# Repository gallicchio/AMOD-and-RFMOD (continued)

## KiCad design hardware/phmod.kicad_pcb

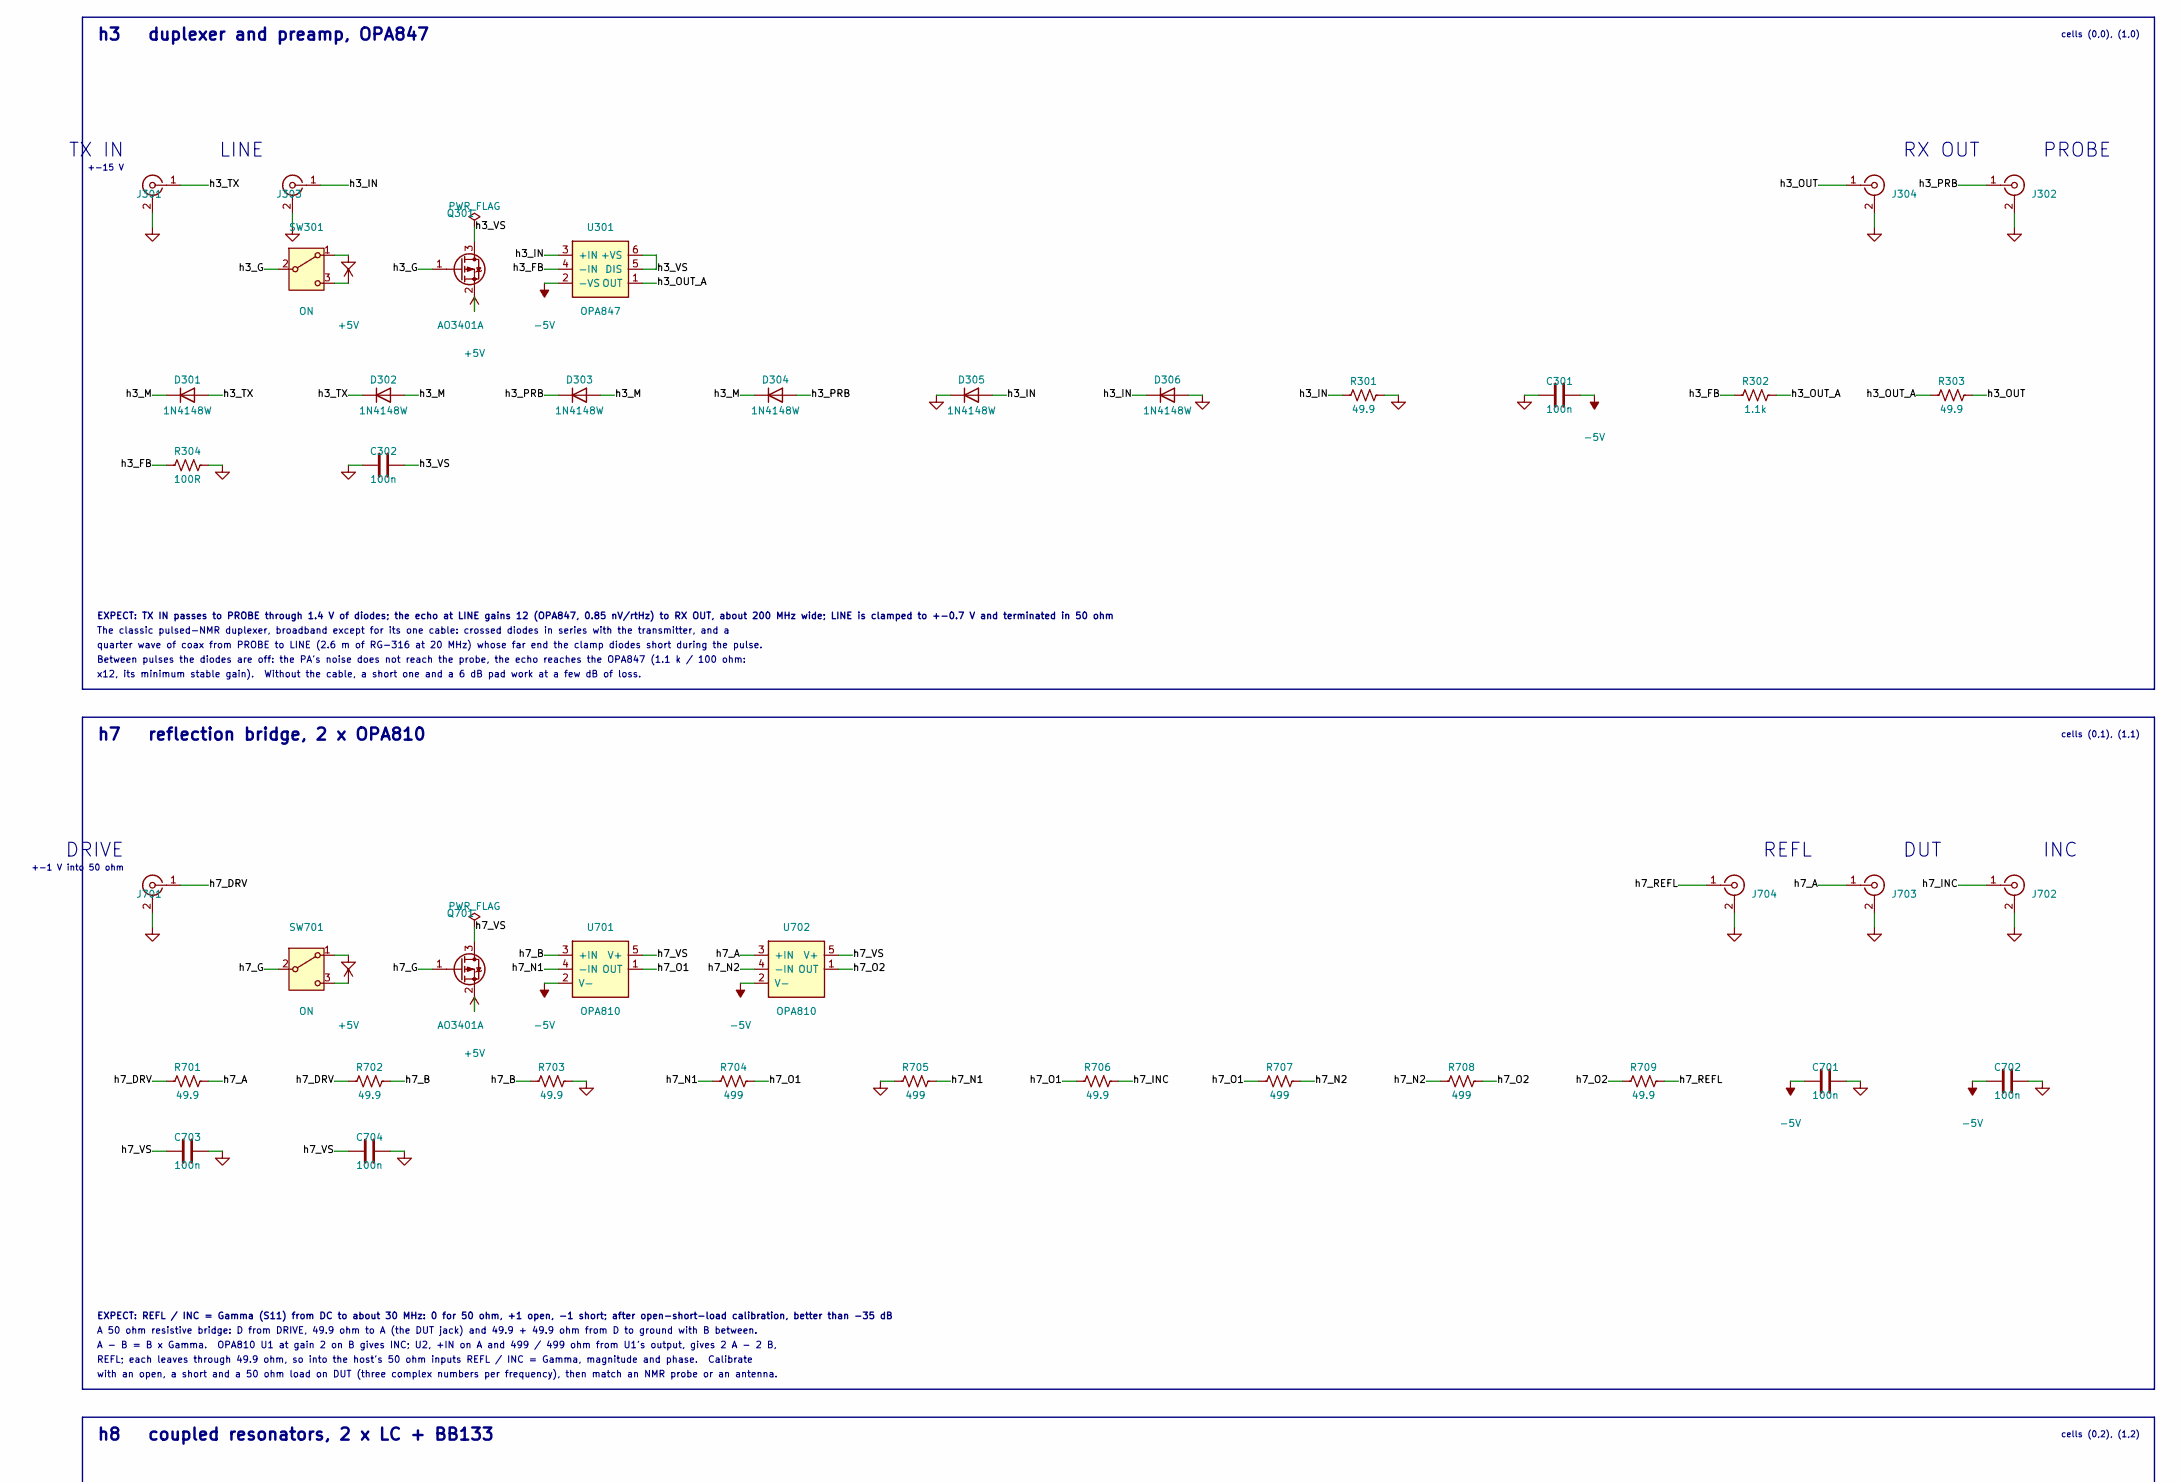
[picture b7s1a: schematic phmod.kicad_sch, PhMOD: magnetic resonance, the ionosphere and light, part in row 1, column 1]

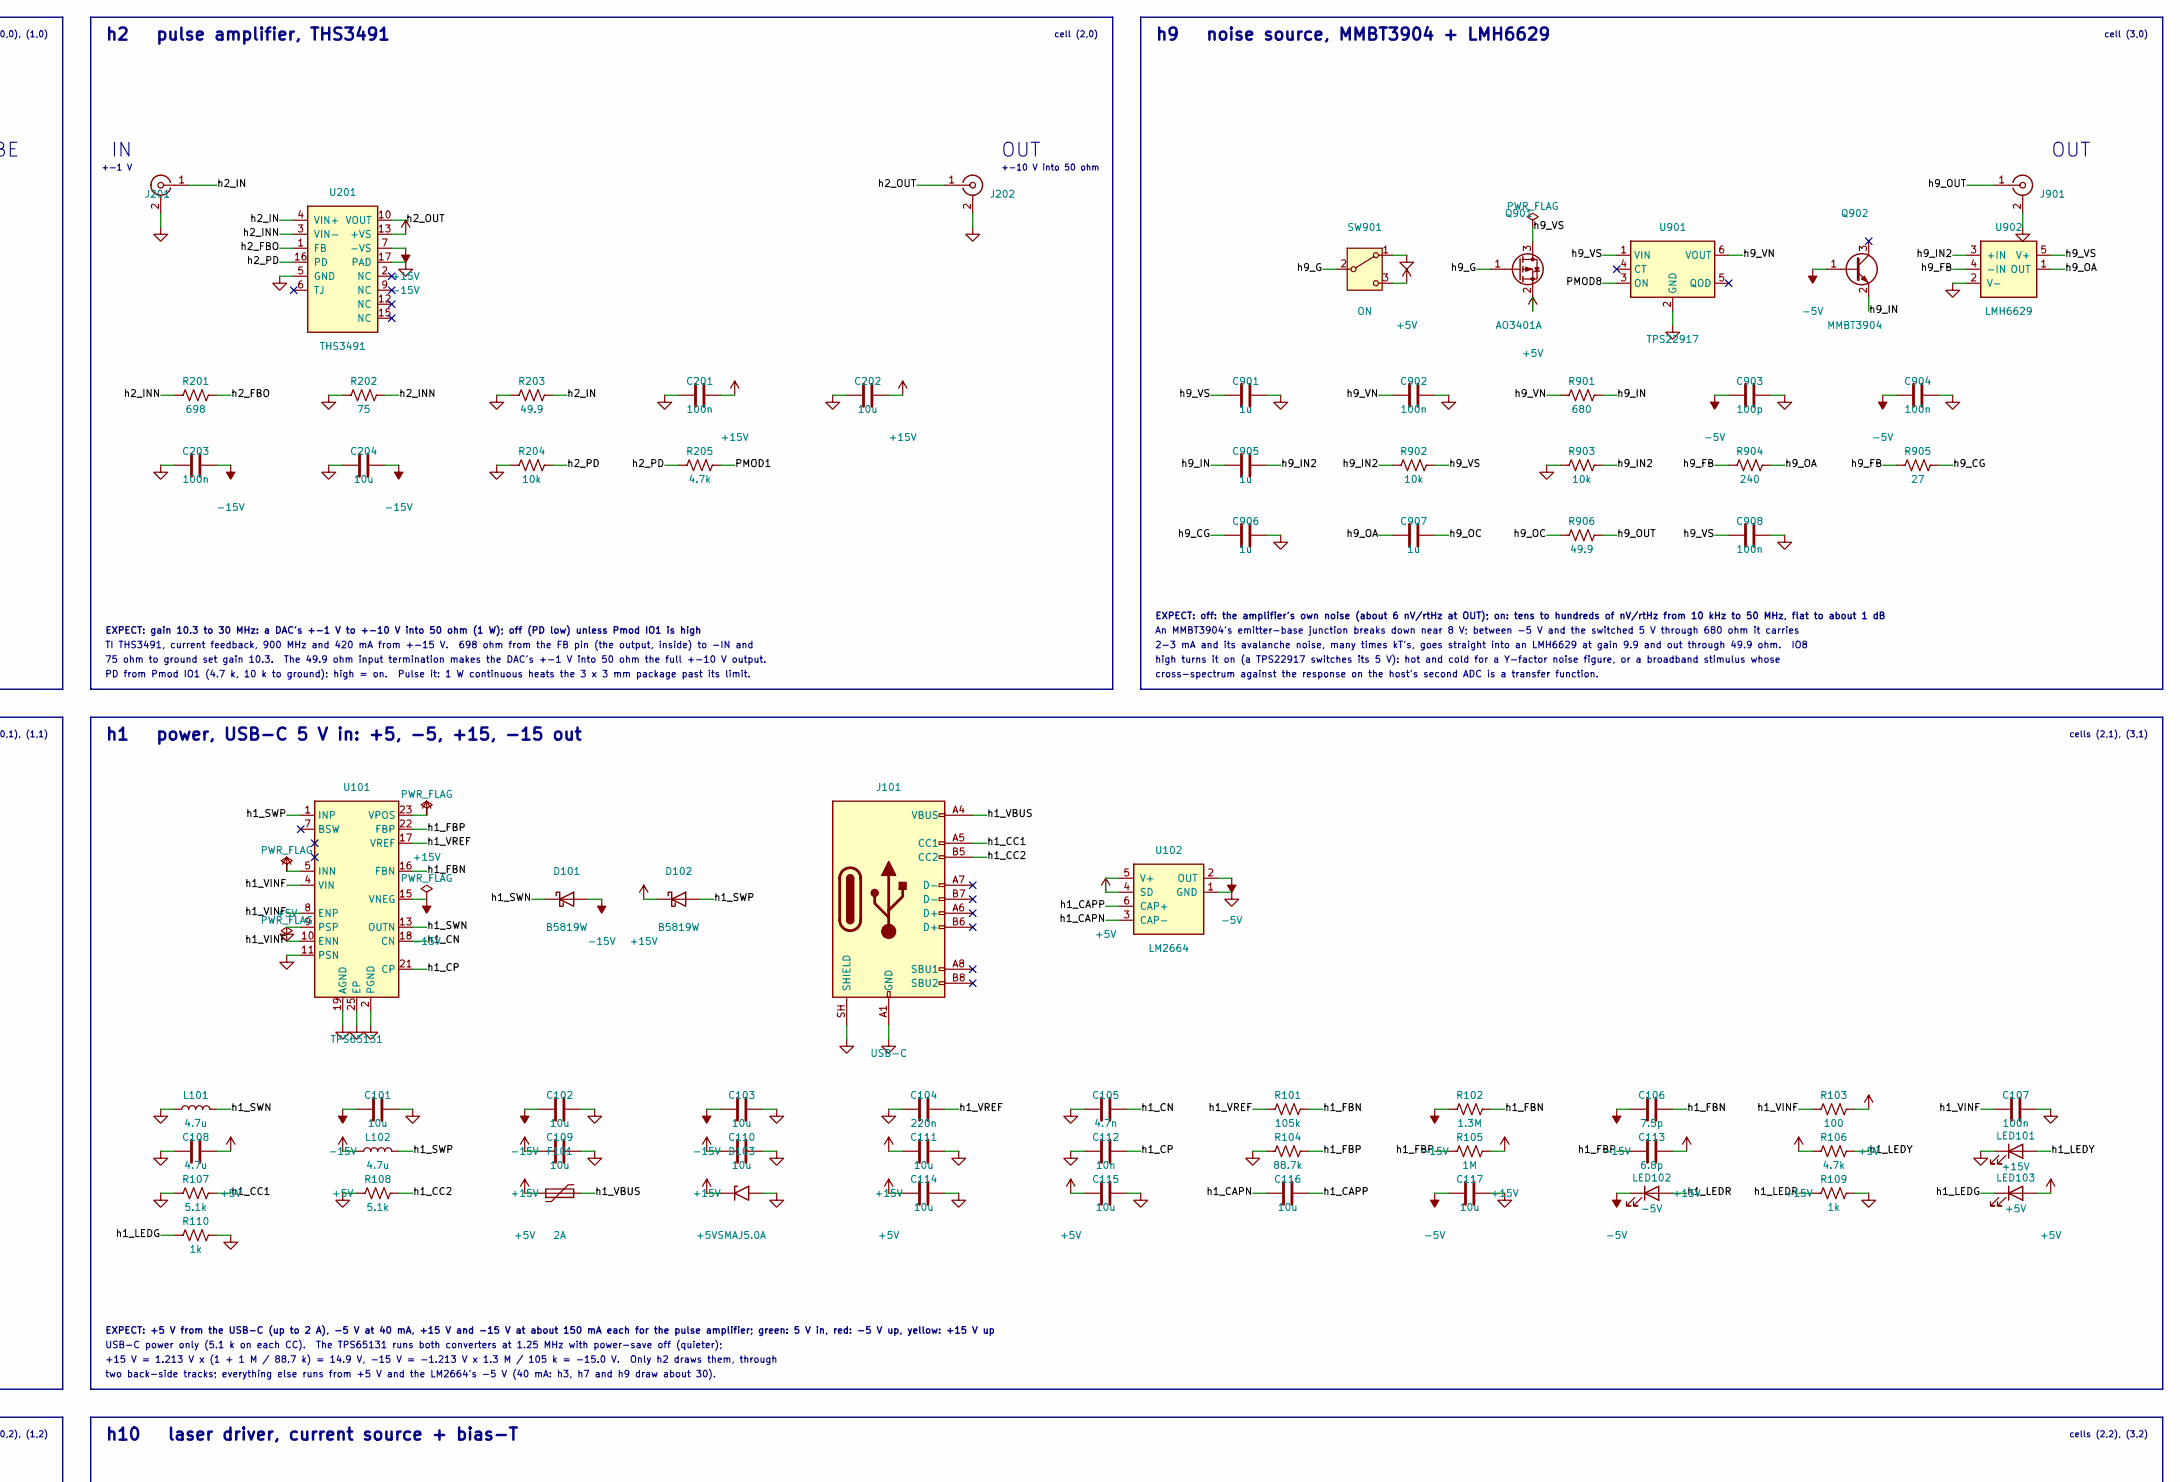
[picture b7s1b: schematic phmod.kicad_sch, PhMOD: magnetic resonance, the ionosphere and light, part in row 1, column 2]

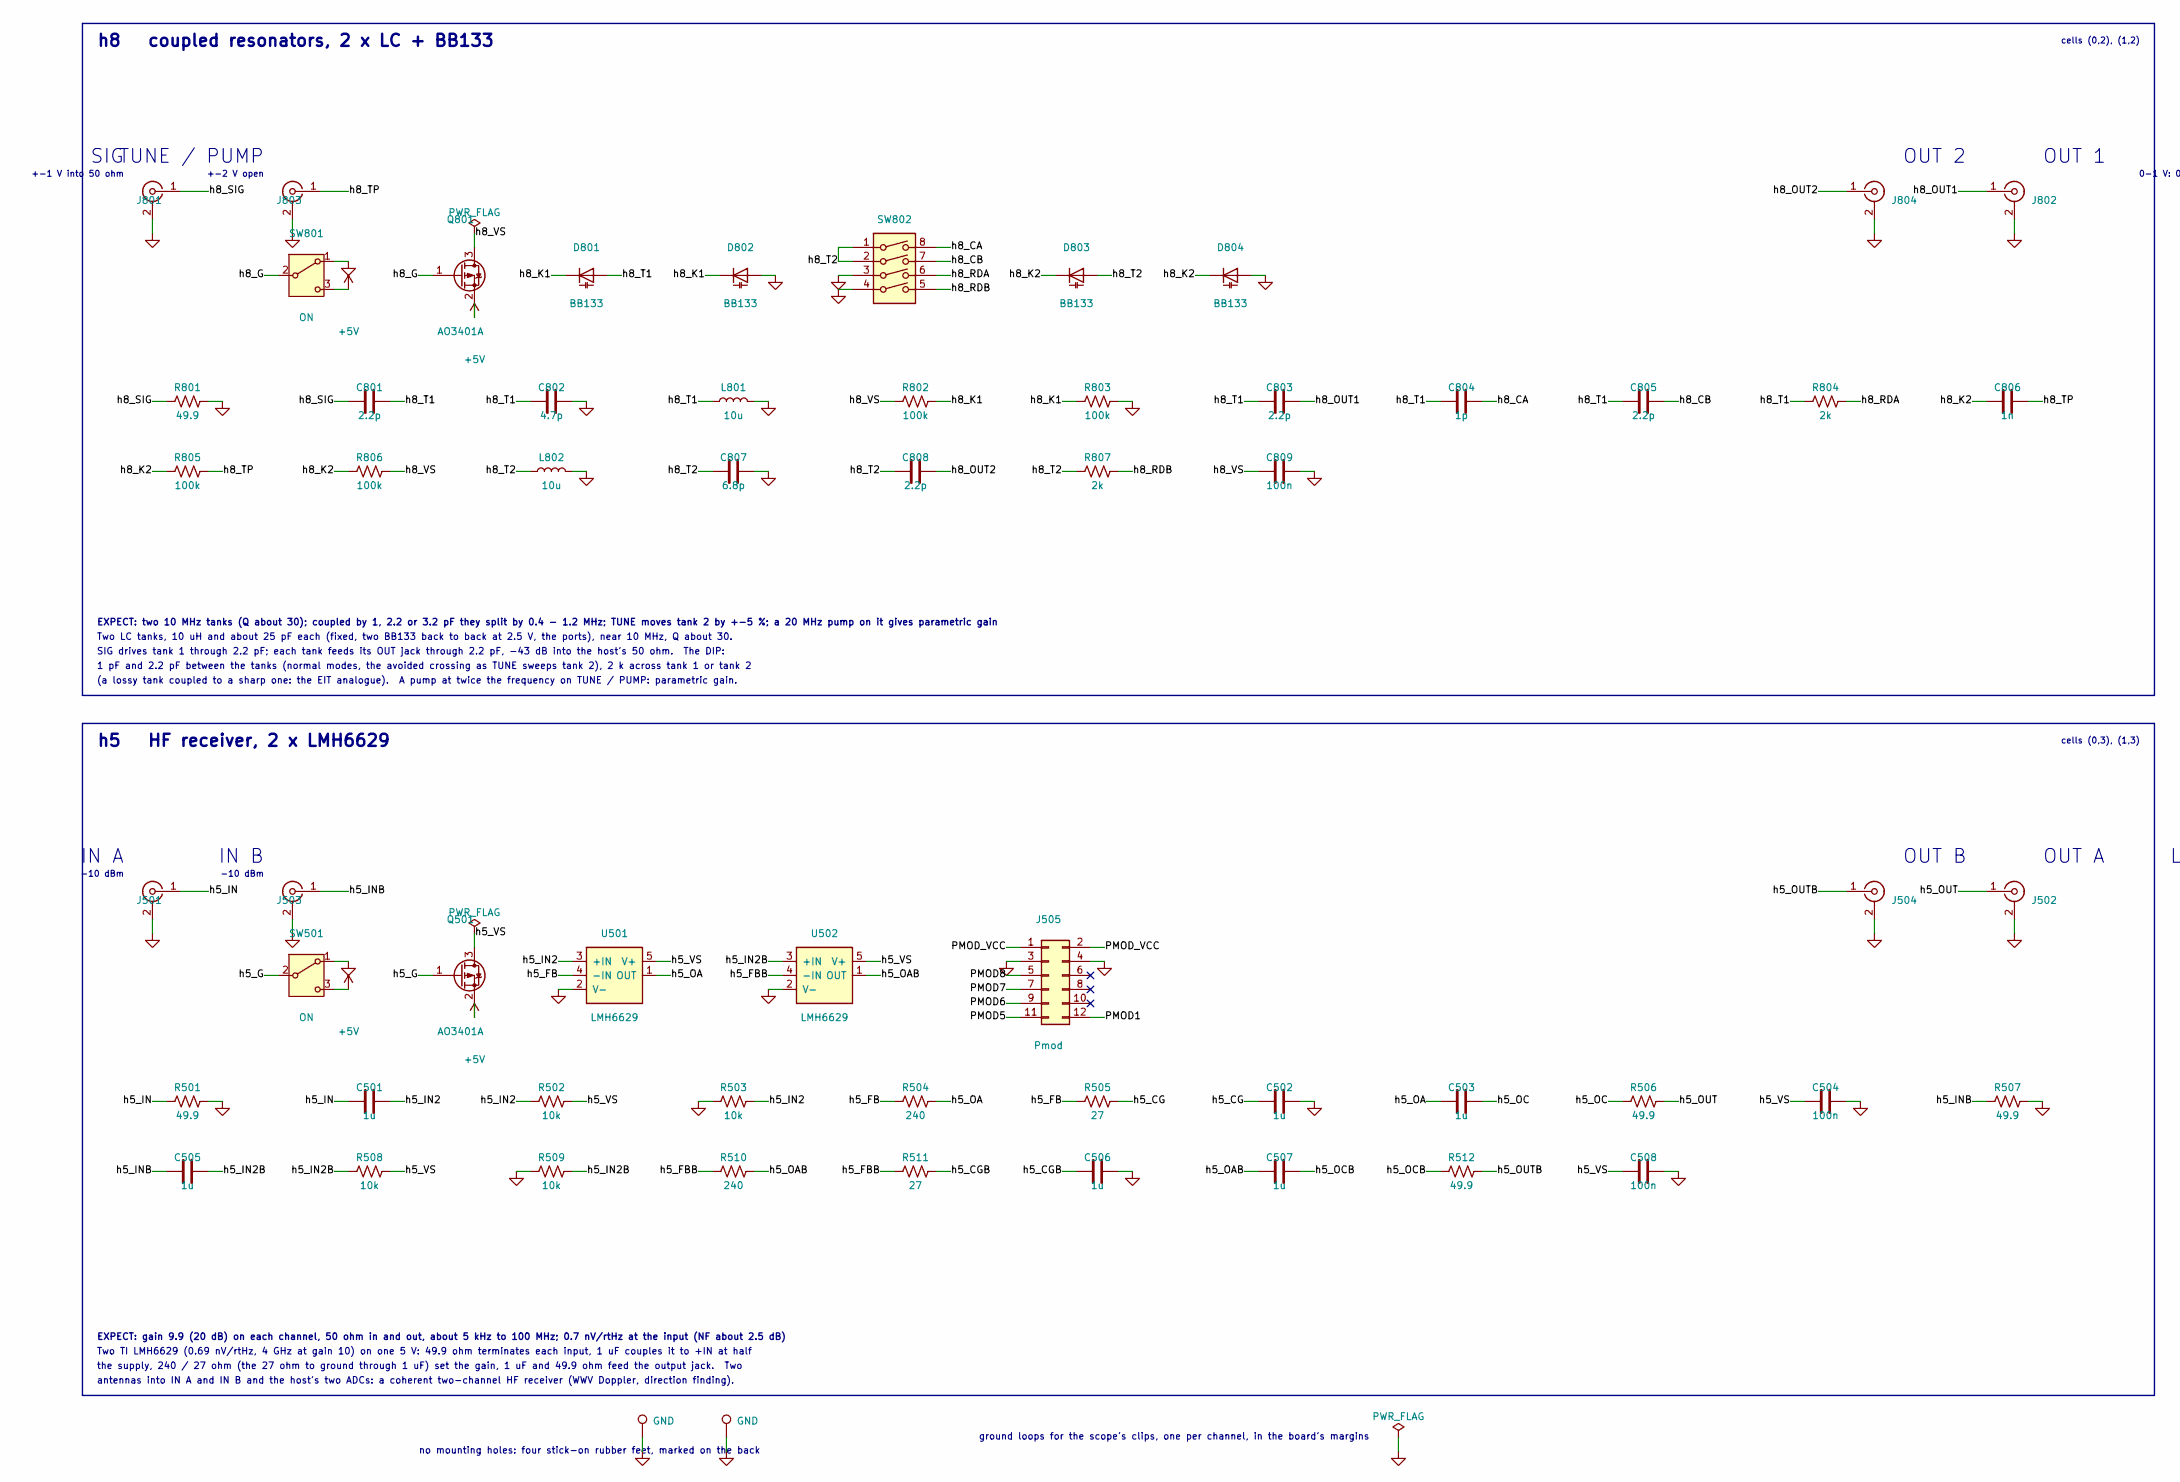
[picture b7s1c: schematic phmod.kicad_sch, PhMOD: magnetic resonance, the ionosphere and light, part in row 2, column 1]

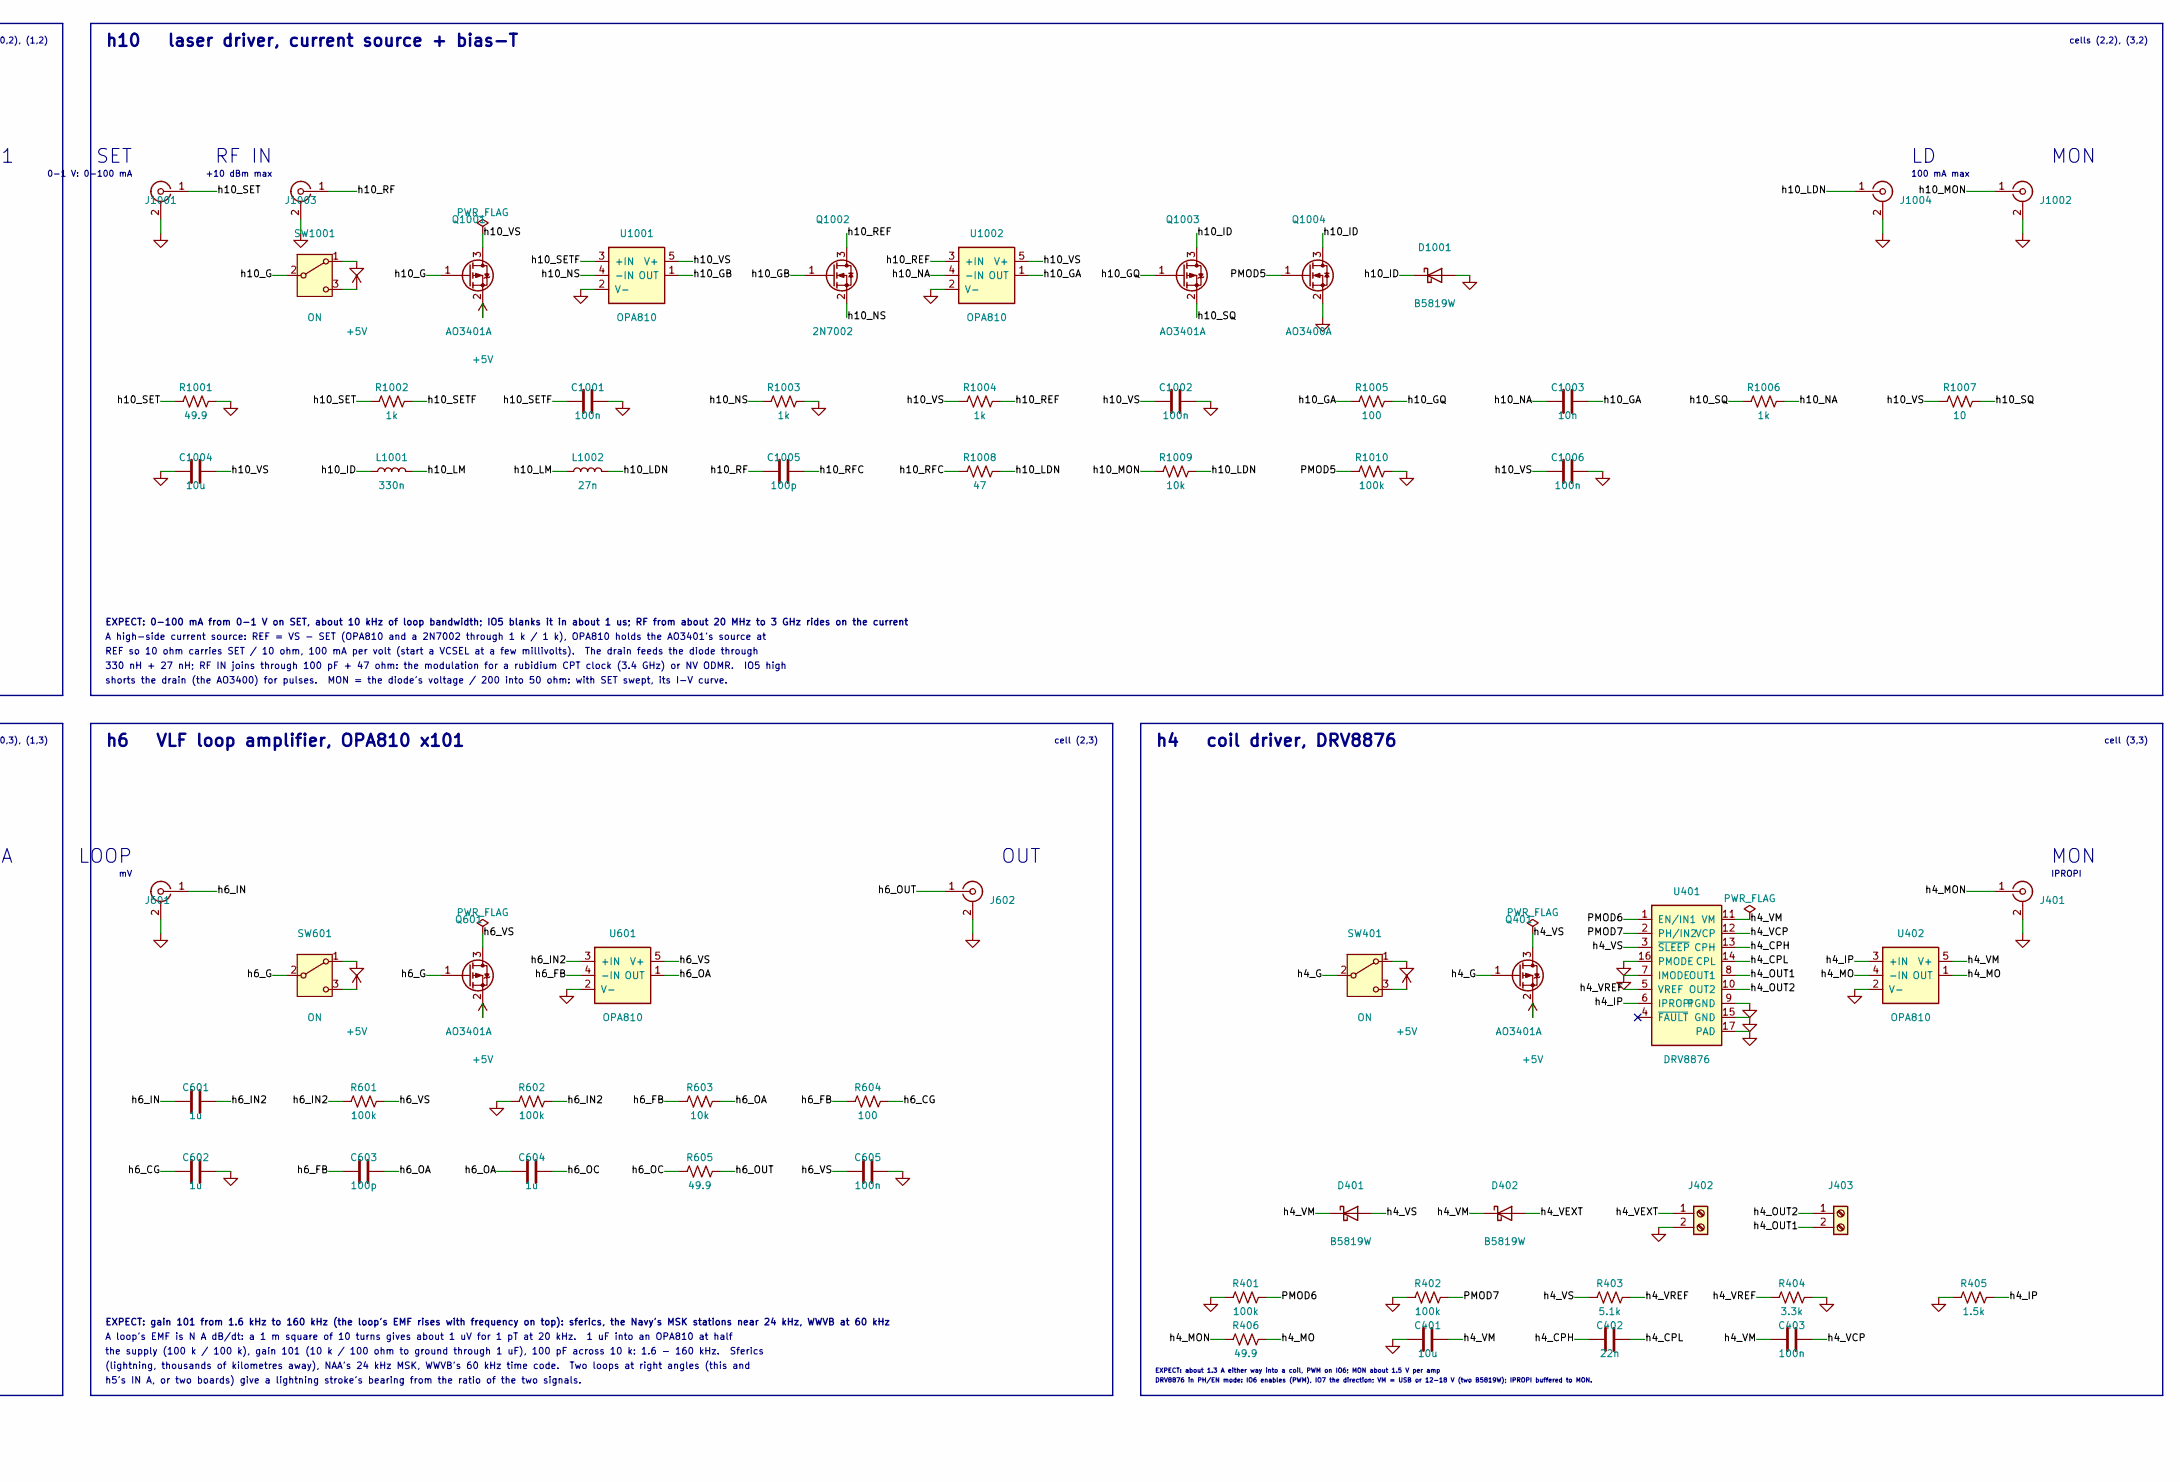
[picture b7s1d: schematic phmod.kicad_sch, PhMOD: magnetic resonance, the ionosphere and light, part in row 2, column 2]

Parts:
C101, C102, C103, C109, C110, C111, C114, C115, C116, C117, C202, C204, C401, C1004: 10u; C_0805_2012Metric; MPN CL21A106KAYNNNE; LCSC C15850
C104: 220n; C_0402_1005Metric; MPN CL05B224KO5NNNC; LCSC C16772
C105: 4.7n; C_0402_1005Metric; MPN CL05B472KB5NNNC; LCSC C84705
C106: 7.5p; C_0402_1005Metric; MPN 0402CG7R5C500NT; LCSC C43514
C107, C201, C203, C403, C504, C508, C605, C701, C702, C703, C704, C809, C902, C904, C908, C1001, C1002, C1006: 100n; C_0402_1005Metric; MPN CL05B104KO5NNNC; LCSC C1525
C108: 4.7u; C_0805_2012Metric; MPN CL21A475KAQNNNE; LCSC C1779
C112, C1003: 10n; C_0402_1005Metric; MPN CL05B103KB5NNNC; LCSC C15195
C113, C807: 6.8p; C_0402_1005Metric; MPN 0402CG6R8C500NT; LCSC C1576
C301, C302: 100n; C_0603_1608Metric; MPN CC0603KRX7R9BB104; LCSC C14663
C402: 22n; C_0402_1005Metric; MPN CL05B223KB5NNNC; LCSC C337699
C501, C502, C503, C505, C506, C507, C601, C602, C604, C901, C905, C906, C907: 1u; C_0402_1005Metric; MPN CL05A105KP5NNNC; LCSC C14445
C603, C903, C1005: 100p; C_0402_1005Metric; MPN 0402CG101J500NT; LCSC C1546
C801, C803, C805, C808: 2.2p; C_0402_1005Metric; MPN 0402CG2R2C500NT; LCSC C1559
C802: 4.7p; C_0402_1005Metric; MPN 0402CG4R7C500NT; LCSC C1569
C804: 1p; C_0402_1005Metric; MPN 0402CG1R0C500NT; LCSC C1550
C806: 1n; C_0402_1005Metric; MPN 0402B102K500NT; LCSC C1523
D101, D102, D401, D402, D1001: B5819W; D_SOD-123; MPN B5819W; LCSC C64885
D103: SMAJ5.0A; D_SMA; MPN SMAJ5.0A; LCSC C78401
D301, D302, D303, D304, D305, D306: 1N4148W; D_SOD-123; MPN 1N4148W; LCSC C81598
D801, D802, D803, D804: BB133; D_SOD-323; MPN BB133; LCSC C5334579
F101: 2A; Fuse_1812_4532Metric; MPN MF-MSMF200-2; LCSC C210837
J101: USB-C; USB_C_Receptacle_HRO_TYPE-C-31-M-12; MPN TYPE-C-31-M-12; LCSC C165948
J201, J202, J301, J302, J303, J304, J401, J501, J502, J503, J504, J601, J602, J701, J702, J703, J704, J801, J802, J803, J804, J901, J1001, J1002, J1003, J1004: SMA; SMA_BWSMA-KE-Z001_Vertical; MPN BWSMA-KE-Z001; LCSC C496549
J402: VM in; TerminalBlock_KF301_1x02_P5.00mm; MPN KF301-5.0-2P; LCSC C474881
J403: coil; TerminalBlock_KF301_1x02_P5.00mm; MPN KF301-5.0-2P; LCSC C474881
J505: Pmod; PinHeader_2x06_P2.54mm_Horizontal_PZ254R-12-12P; MPN PZ254R-12-12P; LCSC C492434
L101, L102: 4.7u; L_4x4_XRNR4030; MPN SWPA4030S4R7MT; LCSC C57269
L801, L802: 10u; L_1210_3225Metric; MPN NLV32T-100J-PF; LCSC C76835
L1001: 330n; L_0805_2012Metric; MPN SDWL2012CR33JSTF; LCSC C98210
L1002: 27n; L_0402_1005Metric; MPN LQW15AN27NG80D; LCSC C882469
LED101: +15V; LED_0805_2012Metric_Kbar; MPN KT-0805Y; LCSC C2296
LED102: -5V; LED_0805_2012Metric_Kbar; MPN NCD0805R1; LCSC C84256
LED103: +5V; LED_0805_2012Metric_Kbar; MPN KT-0805G; LCSC C2297
Q301, Q401, Q501, Q601, Q701, Q801, Q901, Q1001, Q1003: AO3401A; SOT-23; MPN AO3401A; LCSC C15127
Q902: MMBT3904; SOT-23; MPN MMBT3904(RANGE:100-300); LCSC C20526
Q1002: 2N7002; SOT-23; MPN 2N7002; LCSC C8545
Q1004: AO3400A; SOT-23; MPN AO3400A; LCSC C20917
R101: 105k; R_0402_1005Metric; MPN 0402WGF1053TCE; LCSC C25742
R102: 1.3M; R_0402_1005Metric; MPN 0402WGF1304TCE; LCSC C423245
R103, R604, R1005: 100; R_0402_1005Metric; MPN 0402WGF1000TCE; LCSC C25076
R104: 88.7k; R_0402_1005Metric; MPN 0402WGF8872TCE; LCSC C25922
R105: 1M; R_0402_1005Metric; MPN 0402WGF1004TCE; LCSC C26083
R106: 4.7k; R_0805_2012Metric; MPN 0805W8F4701T5E; LCSC C17673
R107, R108: 5.1k; R_0805_2012Metric; MPN 0805W8F5101T5E; LCSC C27834
R109, R110: 1k; R_0805_2012Metric; MPN 0805W8F1001T5E; LCSC C17513
R201: 698; R_0402_1005Metric; MPN 0402WGF6980TCE; LCSC C33359
R202: 75; R_0402_1005Metric; MPN 0402WGF750JTCE; LCSC C25133
R203, R301, R406, R501, R506, R507, R512, R605, R701, R702, R703, R706, R709, R801, R906, R1001: 49.9; R_0402_1005Metric; MPN CRCW040249R9FKEDHP; LCSC C844112
R204, R502, R503, R508, R509, R603, R902, R903, R1009: 10k; R_0402_1005Metric; MPN 0402WGF1002TCE; LCSC C25744
R205: 4.7k; R_0402_1005Metric; MPN 0402WGF4701TCE; LCSC C25900
R302: 1.1k; R_0603_1608Metric; MPN 0603WAF1101T5E; LCSC C22764
R303: 49.9; R_0603_1608Metric; MPN SR0603FR-7T49R9L; LCSC C6230117
R304: 100R; R_0603_1608Metric; MPN 0603WAF1000T5E; LCSC C22775
R401, R402, R601, R602, R802, R803, R805, R806, R1010: 100k; R_0402_1005Metric; MPN 0402WGF1003TCE; LCSC C25741
R403: 5.1k; R_0402_1005Metric; MPN 0402WGF5101TCE; LCSC C25905
R404: 3.3k; R_0402_1005Metric; MPN 0402WGF3301TCE; LCSC C25890
R405: 1.5k; R_0402_1005Metric; MPN 0402WGF1501TCE; LCSC C25867
R504, R510, R904: 240; R_0402_1005Metric; MPN 0402WGF2400TCE; LCSC C25094
R505, R511, R905: 27; R_0402_1005Metric; MPN CR0402FF27R0G; LCSC C100353
R704, R705, R707, R708: 499; R_0402_1005Metric; MPN 0402WGF4990TCE; LCSC C4125
R804, R807: 2k; R_0402_1005Metric; MPN 0402WGF2001TCE; LCSC C4109
R901: 680; R_0402_1005Metric; MPN 0402WGF6800TCE; LCSC C25130
R1002, R1003, R1004, R1006: 1k; R_0402_1005Metric; MPN 0402WGF1001TCE; LCSC C11702
R1007: 10; R_0805_2012Metric; MPN 0805W8F100JT5E; LCSC C17415
R1008: 47; R_0402_1005Metric; MPN 0402WGF470JTCE; LCSC C25118
SW301, SW401, SW501, SW601, SW701, SW801, SW901, SW1001: ON; SW_SPDT_Shouhan_MSK12C02; MPN MSK12C02; LCSC C431540
SW802: DIP4; SW_DIP_SPSTx04_Slide_1.27mm_DSHP04; MPN DSHP04TSGET; LCSC C40736
TP9901, TP9902: GND; TestPoint_Loop_RH-5019; MPN RH-5019; LCSC C5199800
U101: TPS65131; QFN-24-1EP_4x4mm_P0.5mm_EP2.7x2.7mm; MPN TPS65131RGER; LCSC C87663
U102: LM2664; SOT-23-6; MPN LM2664M6X/NOPB; LCSC C108573
U201: THS3491; QFN-16-1EP_3x3mm_P0.5mm_EP1.7x1.7mm; MPN THS3491IRGTR; LCSC C2058688
U301: OPA847; SOT-23-6; MPN OPA847IDBVT; LCSC C2059024
U401: DRV8876; HTSSOP-16-1EP_4.4x5mm_P0.65mm_EP3.4x5mm_Mask2.66x2.46mm; MPN DRV8876PWPR; LCSC C575551
U402, U601, U701, U702, U1001, U1002: OPA810; SOT-23-5; MPN OPA810IDBVR; LCSC C2833513
U501, U502, U902: LMH6629; SOT-23-5; MPN LMH6629MFX/NOPB; LCSC C2059678
U901: TPS22917; SOT-23-6; MPN TPS22917DBVR; LCSC C2681320

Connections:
+5V: C108.2, C114.1, C115.1, D103.1 (A1), F101.1, L102.1, LED103.2 (A), Q301.2 (S), Q401.2 (S), Q501.2 (S), Q601.2 (S), Q701.2 (S), Q801.2 (S), Q901.2 (S), Q1001.2 (S), R103.2, SW301.3 (C), SW401.3 (C), SW501.3 (C), SW601.3 (C), SW701.3 (C), SW801.3 (C), SW901.3 (C), SW1001.3 (C), U101.5 (INN), U101.6 (INN), U102.4 (SD), U102.5 (V+)
+15V: C109.1, C110.1, C111.1, C113.2, C201.2, C202.2, D102.1 (K), R105.2, R106.1, U101.23 (VPOS), U201.13 (+VS), U201.14 (+VS)
-5V: C117.1, C301.2, C701.1, C702.1, C903.1, C904.1, LED102.1 (K), Q902.1 (B), U102.2 (OUT), U301.2 (-VS), U701.2 (V-), U702.2 (V-)
-15V: C101.1, C102.1, C103.1, C106.1, C203.2, C204.2, D101.2 (A), R102.1, U101.15 (VNEG), U201.7 (-VS), U201.8 (-VS)
/PMOD1: J505.12, R205.2
/PMOD5: J505.11, Q1004.1 (G), R1010.1
/PMOD6: J505.9, R401.2, U401.1 (EN/IN1)
/PMOD7: J505.7, R402.2, U401.2 (PH/IN2)
/PMOD8: J505.5, U901.3 (ON)
/PMOD_VCC: J505.1, J505.2
/h1_CAPN: C116.1, U102.3 (CAP-)
/h1_CAPP: C116.2, U102.6 (CAP+)
/h1_CC1: J101.A5 (CC1), R107.2
/h1_CC2: J101.B5 (CC2), R108.2
/h1_CN: C105.2, U101.18 (CN)
/h1_CP: C112.2, U101.21 (CP)
/h1_FBN: C106.2, R101.2, R102.2, U101.16 (FBN)
/h1_FBP: C113.1, R104.2, R105.1, U101.22 (FBP)
/h1_LEDG: LED103.1 (K), R110.1
/h1_LEDR: LED102.2 (A), R109.1
/h1_LEDY: LED101.2 (A), R106.2
/h1_SWN: D101.1 (K), L101.2, U101.13 (OUTN), U101.14 (OUTN)
/h1_SWP: D102.2 (A), L102.2, U101.1 (INP), U101.24 (INP)
/h1_VBUS: F101.2, J101.A4 (VBUS), J101.A9 (VBUS), J101.B4 (VBUS), J101.B9 (VBUS)
/h1_VINF: C107.1, R103.1, U101.4 (VIN), U101.8 (ENP), U101.10 (ENN)
/h1_VREF: C104.2, R101.1, U101.17 (VREF)
/h2_FBO: R201.2, U201.1 (FB)
/h2_IN: J201.1 (In), R203.2, U201.4 (VIN+)
/h2_INN: R201.1, R202.2, U201.3 (VIN-)
/h2_OUT: J202.1 (In), U201.10 (VOUT), U201.11 (VOUT)
/h2_PD: R204.2, R205.1, U201.16 (PD)
/h3_FB: R302.1, R304.1, U301.4 (-IN)
/h3_G: Q301.1 (G), SW301.2 (B)
/h3_IN: D305.2 (A), D306.1 (K), J303.1 (In), R301.1, U301.3 (+IN)
/h3_M: D301.1 (K), D302.2 (A), D303.2 (A), D304.1 (K)
/h3_OUT: J304.1 (In), R303.2
/h3_OUT_A: R302.2, R303.1, U301.1 (OUT)
/h3_PRB: D303.1 (K), D304.2 (A), J302.1 (In)
/h3_TX: D301.2 (A), D302.1 (K), J301.1 (In)
/h3_VS: C302.2, Q301.3 (D), U301.5 (DIS), U301.6 (+VS)
/h4_CPH: C402.1, U401.13 (CPH)
/h4_CPL: C402.2, U401.14 (CPL)
/h4_G: Q401.1 (G), SW401.2 (B)
/h4_IP: R405.2, U401.6 (IPROPI), U402.3 (+IN)
/h4_MO: R406.2, U402.1 (OUT), U402.4 (-IN)
/h4_MON: J401.1 (In), R406.1
/h4_OUT1: J403.2, U401.8 (OUT1)
/h4_OUT2: J403.1, U401.10 (OUT2)
/h4_VCP: C403.2, U401.12 (VCP)
/h4_VEXT: D402.2 (A), J402.1
/h4_VM: C401.2, C403.1, D401.1 (K), D402.1 (K), U401.11 (VM), U402.5 (V+)
/h4_VREF: R403.2, R404.1, U401.5 (VREF)
/h4_VS: D401.2 (A), Q401.3 (D), R403.1, U401.3 (~SLEEP)
/h5_CG: C502.1, R505.2
/h5_CGB: C506.1, R511.2
/h5_FB: R504.1, R505.1, U501.4 (-IN)
/h5_FBB: R510.1, R511.1, U502.4 (-IN)
/h5_G: Q501.1 (G), SW501.2 (B)
/h5_IN: C501.1, J501.1 (In), R501.1
/h5_IN2: C501.2, R502.1, R503.2, U501.3 (+IN)
/h5_IN2B: C505.2, R508.1, R509.2, U502.3 (+IN)
/h5_INB: C505.1, J503.1 (In), R507.1
/h5_OA: C503.1, R504.2, U501.1 (OUT)
/h5_OAB: C507.1, R510.2, U502.1 (OUT)
/h5_OC: C503.2, R506.1
/h5_OCB: C507.2, R512.1
/h5_OUT: J502.1 (In), R506.2
/h5_OUTB: J504.1 (In), R512.2
/h5_VS: C504.1, C508.1, Q501.3 (D), R502.2, R508.2, U501.5 (V+), U502.5 (V+)
/h6_CG: C602.1, R604.2
/h6_FB: C603.1, R603.1, R604.1, U601.4 (-IN)
/h6_G: Q601.1 (G), SW601.2 (B)
/h6_IN: C601.1, J601.1 (In)
/h6_IN2: C601.2, R601.1, R602.2, U601.3 (+IN)
/h6_OA: C603.2, C604.1, R603.2, U601.1 (OUT)
/h6_OC: C604.2, R605.1
/h6_OUT: J602.1 (In), R605.2
/h6_VS: C605.1, Q601.3 (D), R601.2, U601.5 (V+)
/h7_A: J703.1 (In), R701.2, U702.3 (+IN)
/h7_B: R702.2, R703.1, U701.3 (+IN)
/h7_DRV: J701.1 (In), R701.1, R702.1
/h7_G: Q701.1 (G), SW701.2 (B)
/h7_INC: J702.1 (In), R706.2
/h7_N1: R704.1, R705.2, U701.4 (-IN)
/h7_N2: R707.2, R708.1, U702.4 (-IN)
/h7_O1: R704.2, R706.1, R707.1, U701.1 (OUT)
/h7_O2: R708.2, R709.1, U702.1 (OUT)
/h7_REFL: J704.1 (In), R709.2
/h7_VS: C703.1, C704.1, Q701.3 (D), U701.5 (V+), U702.5 (V+)
/h8_CA: C804.2, SW802.8
/h8_CB: C805.2, SW802.7
/h8_G: Q801.1 (G), SW801.2 (B)
/h8_K1: D801.1 (K), D802.1 (K), R802.2, R803.1
/h8_K2: C806.1, D803.1 (K), D804.1 (K), R805.1, R806.1
/h8_OUT1: C803.2, J802.1 (In)
/h8_OUT2: C808.2, J804.1 (In)
/h8_RDA: R804.2, SW802.6
/h8_RDB: R807.2, SW802.5
/h8_SIG: C801.1, J801.1 (In), R801.1
/h8_T1: C801.2, C802.1, C803.1, C804.1, C805.1, D801.2 (A), L801.1, R804.1
/h8_T2: C807.1, C808.1, D803.2 (A), L802.1, R807.1, SW802.1, SW802.2
/h8_TP: C806.2, J803.1 (In), R805.2
/h8_VS: C809.1, Q801.3 (D), R802.1, R806.2
/h9_CG: C906.1, R905.2
/h9_FB: R904.1, R905.1, U902.4 (-IN)
/h9_G: Q901.1 (G), SW901.2 (B)
/h9_IN: C905.1, Q902.2 (E), R901.2
/h9_IN2: C905.2, R902.1, R903.2, U902.3 (+IN)
/h9_OA: C907.1, R904.2, U902.1 (OUT)
/h9_OC: C907.2, R906.1
/h9_OUT: J901.1 (In), R906.2
/h9_VN: C902.1, R901.1, U901.6 (VOUT)
/h9_VS: C901.1, C908.1, Q901.3 (D), R902.2, U901.1 (VIN), U902.5 (V+)
/h10_G: Q1001.1 (G), SW1001.2 (B)
/h10_GA: C1003.2, R1005.1, U1002.1 (OUT)
/h10_GB: Q1002.1 (G), U1001.1 (OUT)
/h10_GQ: Q1003.1 (G), R1005.2
/h10_ID: D1001.1 (K), L1001.1, Q1003.3 (D), Q1004.3 (D)
/h10_LDN: J1004.1 (In), L1002.2, R1008.2, R1009.2
/h10_LM: L1001.2, L1002.1
/h10_MON: J1002.1 (In), R1009.1
/h10_NA: C1003.1, R1006.2, U1002.4 (-IN)
/h10_NS: Q1002.2 (S), R1003.1, U1001.4 (-IN)
/h10_REF: Q1002.3 (D), R1004.2, U1002.3 (+IN)
/h10_RF: C1005.1, J1003.1 (In)
/h10_RFC: C1005.2, R1008.1
/h10_SET: J1001.1 (In), R1001.1, R1002.1
/h10_SETF: C1001.1, R1002.2, U1001.3 (+IN)
/h10_SQ: Q1003.2 (S), R1006.1, R1007.2
/h10_VS: C1002.1, C1004.2, C1006.1, Q1001.3 (D), R1004.1, R1007.1, U1001.5 (V+), U1002.5 (V+)
GND: C101.2, C102.2, C103.2, C104.1, C105.1, C107.2, C108.1, C109.2, C110.2, C111.2, C112.1, C114.2, C115.2, C117.2, C201.1, C202.1, C203.1, C204.1, C301.1, C302.1, C401.1, C502.2, C504.2, C506.2, C508.2, C602.2, C605.2, C701.2, C702.2, C703.2, C704.2, C802.2, C807.2, C809.2, C901.2, C902.2, C903.2, C904.2, C906.2, C908.2, C1001.2, C1002.2, C1004.1, C1006.2, D103.2 (A2), D305.1 (K), D306.2 (A), D802.2 (A), D804.2 (A), D1001.2 (A), J101.A1 (GND), J101.A12 (GND), J101.B1 (GND), J101.B12 (GND), J101.SH (SHIELD), J201.2 (Ext), J202.2 (Ext), J301.2 (Ext), J302.2 (Ext), J303.2 (Ext), J304.2 (Ext), J401.2 (Ext), J402.2, J501.2 (Ext), J502.2 (Ext), J503.2 (Ext), J504.2 (Ext), J505.3, J505.4, J601.2 (Ext), J602.2 (Ext), J701.2 (Ext), J702.2 (Ext), J703.2 (Ext), J704.2 (Ext), J801.2 (Ext), J802.2 (Ext), J803.2 (Ext), J804.2 (Ext), J901.2 (Ext), J1001.2 (Ext), J1002.2 (Ext), J1003.2 (Ext), J1004.2 (Ext), L101.1, L801.2, L802.2, LED101.1 (K), Q1004.2 (S), R104.1, R107.1, R108.1, R109.2, R110.2, R202.1, R203.1, R204.1, R301.2, R304.2, R401.1, R402.1, R404.2, R405.1, R501.2, R503.1, R507.2, R509.1, R602.1, R703.2, R705.1, R801.2, R803.2, R903.1, R1001.2, R1003.2, R1010.2, SW301.1 (A), SW401.1 (A), SW501.1 (A), SW601.1 (A), SW701.1 (A), SW801.1 (A), SW802.3, SW802.4, SW901.1 (A), SW1001.1 (A), TP9901.1, TP9902.1, U101.2 (PGND), U101.3 (PGND), U101.9 (PSP), U101.11 (PSN), U101.19 (AGND), U101.25 (EP), U102.1 (GND), U201.5 (GND), U201.17 (PAD), U401.7 (IMODE), U401.9 (PGND), U401.15 (GND), U401.16 (PMODE), U401.17 (PAD), U402.2 (V-), U501.2 (V-), U502.2 (V-), U601.2 (V-), U901.2 (GND), U902.2 (V-), U1001.2 (V-), U1002.2 (V-)

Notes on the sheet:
PD from Pmod IO1 (4.7 k, 10 k to ground): high = on. Pulse it: 1 W continuous heats the 3 x 3 mm package past its limit.
cells (2,1), (3,1)
LINE
h4 coil driver, DRV8876
Two TI LMH6629 (0.69 nV/rtHz, 4 GHz at gain 10) on one 5 V: 49.9 ohm terminates each input, 1 uF couples it to +IN at half
h10 laser driver, current source + bias-T
330 nH + 27 nH; RF IN joins through 100 pF + 47 ohm: the modulation for a rubidium CPT clock (3.4 GHz) or NV ODMR. IO5 high
USB-C power only (5.1 k on each CC). The TPS65131 runs both converters at 1.25 MHz with power-save off (quieter);
cells (2,2), (3,2)
high turns it on (a TPS22917 switches its 5 V): hot and cold for a Y-factor noise figure, or a broadband stimulus whose
(lightning, thousands of kilometres away), NAA's 24 kHz MSK, WWVB's 60 kHz time code. Two loops at right angles (this and
A high-side current source: REF = VS - SET (OPA810 and a 2N7002 through 1 k / 1 k), OPA810 holds the AO3401's source at
with an open, a short and a 50 ohm load on DUT (three complex numbers per frequency), then match an NMR probe or an antenna.
cell (2,0)
IPROPI
cell (3,3)
h3 duplexer and preamp, OPA847
REFL; each leaves through 49.9 ohm, so into the host's 50 ohm inputs REFL / INC = Gamma, magnitude and phase. Calibrate
+-1 V into 50 ohm
SIG
Two LC tanks, 10 uH and about 25 pF each (fixed, two BB133 back to back at 2.5 V, the ports), near 10 MHz, Q about 30.
IN A
+10 dBm max
OUT 1
h6 VLF loop amplifier, OPA810 x101
RF IN
EXPECT: 0-100 mA from 0-1 V on SET, about 10 kHz of loop bandwidth; IO5 blanks it in about 1 us; RF from about 20 MHz to 3 GHz rides on the current
EXPECT: gain 10.3 to 30 MHz: a DAC's +-1 V to +-10 V into 50 ohm (1 W); off (PD low) unless Pmod IO1 is high
75 ohm to ground set gain 10.3. The 49.9 ohm input termination makes the DAC's +-1 V into 50 ohm the full +-10 V output.
EXPECT: gain 9.9 (20 dB) on each channel, 50 ohm in and out, about 5 kHz to 100 MHz; 0.7 nV/rtHz at the input (NF about 2.5 dB)
cells (0,0), (1,0)
EXPECT: gain 101 from 1.6 kHz to 160 kHz (the loop's EMF rises with frequency on top): sferics, the Navy's MSK stations near 24 kHz, WWVB at 60 kHz
h7 reflection bridge, 2 x OPA810
+15 V = 1.213 V x (1 + 1 M / 88.7 k) = 14.9 V, -15 V = -1.213 V x 1.3 M / 105 k = -15.0 V. Only h2 draws them, through
+-2 V open
100 mA max
h5's IN A, or two boards) give a lightning stroke's bearing from the ratio of the two signals.
TI THS3491, current feedback, 900 MHz and 420 mA from +-15 V. 698 ohm from the FB pin (the output, inside) to -IN and
quarter wave of coax from PROBE to LINE (2.6 m of RG-316 at 20 MHz) whose far end the clamp diodes short during the pulse.
cell (2,3)
